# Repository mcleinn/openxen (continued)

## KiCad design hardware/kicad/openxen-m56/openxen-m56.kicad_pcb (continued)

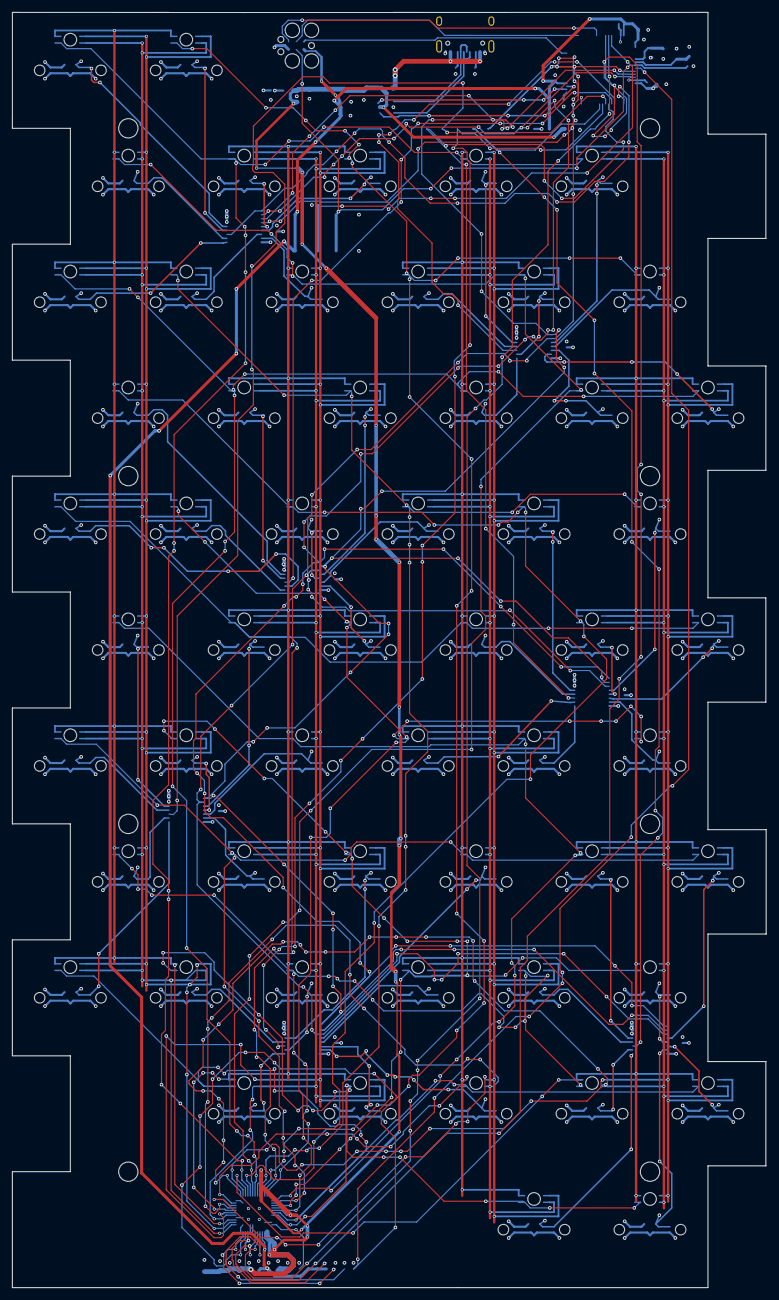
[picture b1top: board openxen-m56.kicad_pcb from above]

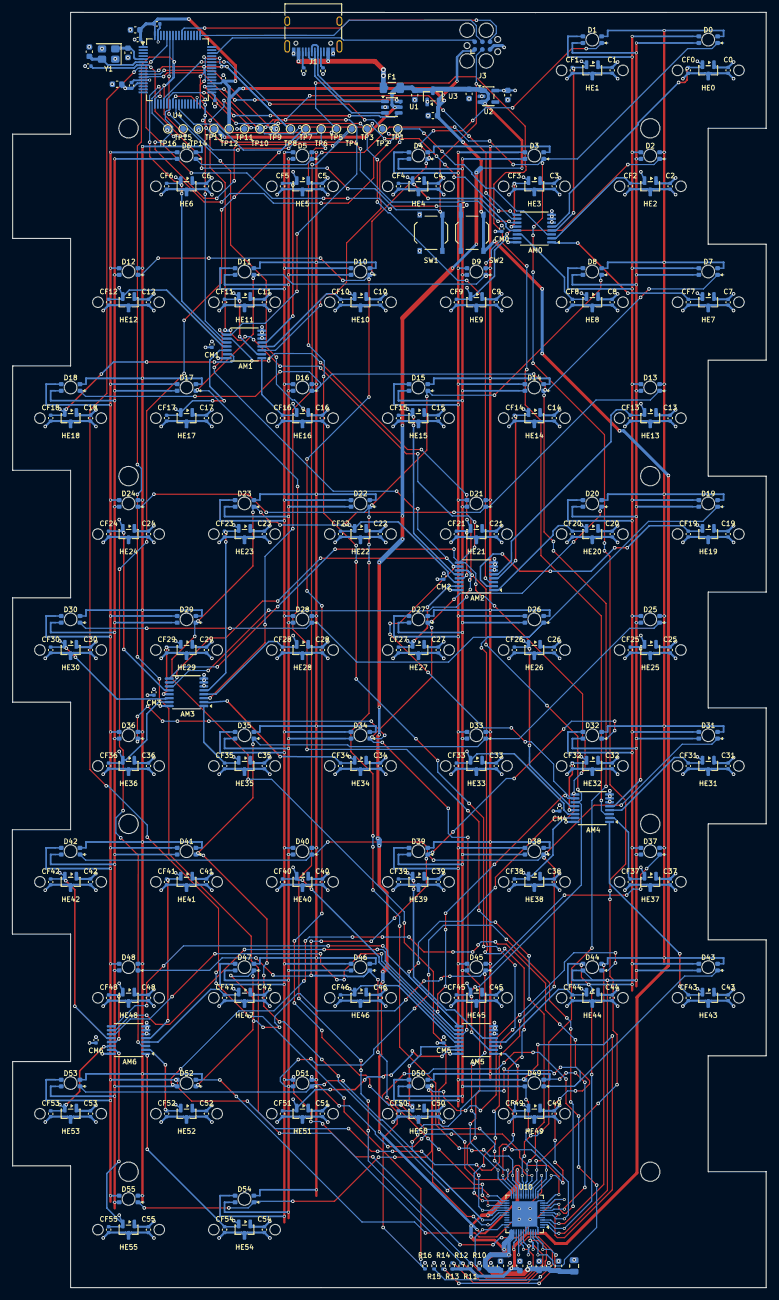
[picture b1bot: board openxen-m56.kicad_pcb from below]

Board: 4 copper layers, 124.8 x 211.2 mm, 362 parts (298 on the bottom side), 118 nets.

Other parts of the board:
H1, H2, H3, H4, H5, H6, H7, H8: MountingHole_3.2mm_M3_NoPad
K0, K1, K2, K3, K4, K5, K6, K7, K8, K9, K10, K11, K12, K13, K14, K15, K16, K17, K18, K19, K20, K21, K22, K23, K24, K25, K26, K27, K28, K29, K30, K31, K32, K33, K34, K35, K36, K37, K38, K39, K40, K41, K42, K43, K44, K45, K46, K47, K48, K49, K50, K51, K52, K53, K54, K55: Lekker Tikken; SW_Lekker_1u

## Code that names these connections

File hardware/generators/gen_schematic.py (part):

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Proven-design policy: nothing on the controller side is drawn from scratch.
* Controller block (MCU, USB-C, ESD, polyfuse, both LDOs, crystal, BOOT/RESET buttons,
  TC2030, JST): copied verbatim from HE60's schematic (region below the key matrix), then
  patched: MUX_OUT_8/9 become no-connects, PB6/PB7/PC0 get the LED driver labels.
* Sensor cell (sensor + 100 nF + 4.7 nF + power + label): HE60's HE1 cell cloned 56×.
* Mux cell (74LV4051 + decoupling + 8 input labels + output + selects): HE60's AM1 cell
  cloned 7×, inputs relabelled from the mux matrix in module.json.
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    matrix = SPEC["mux"]["libhmk_matrix"]  # [mux input][select channel] -> key id + 1 (libhmk keyboard.json order)
    he_in_by_channel = he60_mux_channel_labels(he, am1, mcell, libs)
    for m in range(7):
        label_map = {"MUX_OUT_2": f"MUX_OUT_{m + 1}"}
        for s_ in range(8):
            kid_ = matrix[m][s_]
            label_map[he_in_by_channel[s_]] = f"HE{kid_ - 1}" if kid_ else f"NC_MUX{m}_{s_}"
        ref_map = {r: (f"AM{m}" if r == "AM2" else f"CM{m}") for r in mrefs if not r.startswith("#")}
        stamp(sh_mux, mcell, MUX_ORIGIN[0] + m * MUX_PITCH - mx, MUX_ORIGIN[1] - my, ref_map, label_map)
    sh_mux.text("Mux m serves keys 8m..8m+7 (channel = key - 8m). Select lines PC1..PC3, outputs MUX_OUT_1..7 -> PA3..PA7, PC4, PC5 (HE60 pins).", 20.32, 22.86, 2.0)

    # ---- 3. controller block: everything of HE60 below y = 262 except key/mux cells, verbatim
    ctrl = ks.clone_region(he, -1000, 262.0, 5000, 5000, CTRL_SHIFT[0], CTRL_SHIFT[1], sh_ctrl,
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            add_lcsc(item)
    sh_ctrl.used_libs = {("openxen:" + l.split(":", 1)[1]) if l.startswith("HE60:") else l for l in sh_ctrl.used_libs}
    patch_controller(sh_ctrl, libs)
    sh_ctrl.text("Copied from HE60 v2.1 (GPL-3.0). Changes: F1 2 A fuse, J2 not populated, PB6/PB7 = LED driver I2C, PC0 = LED_SDB, MUX_OUT_8/9 unused.", 20.32, 22.86, 2.0)
    gen_test_points(sh_ctrl, libs)

    # ---- 4. LED sheet
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

def patch_controller(sheet: ks.Sheet, libs: ks.LibSymbols) -> None:
    """MUX_OUT_8/9 -> no-connect; PB6/PB7/PC0 no-connects -> LED driver labels."""
    mcu = [i for i in sheet.items if i[0] == "symbol" and "AT32" in sexp.q(i, "lib_id")][0]
    pts = libs.pin_points(mcu)
    names = {num: name for num, name, *_ in libs.pins(sexp.q(mcu, "lib_id"))}
    want = {"PB6": "LED_SCL", "PB7": "LED_SDA", "PC0": "LED_SDB"}
    # remove the no_connect at those pins and add a label
    targets = {names[n]: p for n, p in pts.items() if names[n] in want}
    keep = []
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    for pin, label in want.items():
        x, y = targets[pin]
        rot = (pin_rot[pin] + 180 + inst_rot) % 360   # label points away from the body (top pins: 90)
        sheet.glabel(label, x, y, rot, "bidirectional" if label != "LED_SDB" else "output")


TEST_POINTS = ["MUX_OUT_1", "MUX_OUT_2", "MUX_OUT_3", "MUX_OUT_4", "MUX_OUT_5", "MUX_OUT_6", "MUX_OUT_7",
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            else:
                sheet.no_connect(x, y)
        elif name == "SDA":
            sheet.glabel("LED_SDA", x, y, side, "bidirectional")
        elif name == "SCL":
            sheet.glabel("LED_SCL", x, y, side, "input")
        elif name == "SDB":
            sheet.glabel("LED_SDB", x, y, side, "input")
        elif name == "INTB":
            sheet.glabel("LED_INTB", x, y, side, "output")
        elif name in ("IICRST", "SYNC"):
            sheet.glabel(f"LED_{name}", x, y, side, "input")
        elif name in ("ADDR1", "ADDR2"):
            gnd_pins.append((x, y))  # I2C address 0: both to GND (datasheet Fig. 2)
        elif name in ("RSET", "R_EXT", "REXT"):
            sheet.glabel("LED_REXT", x, y, side, "passive")
        elif name == "VIO":
            dx = 5.08 if x > ux else -5.08
            sheet.power("power:+3.3V", x + dx, y, 90 if dx < 0 else 270)
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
